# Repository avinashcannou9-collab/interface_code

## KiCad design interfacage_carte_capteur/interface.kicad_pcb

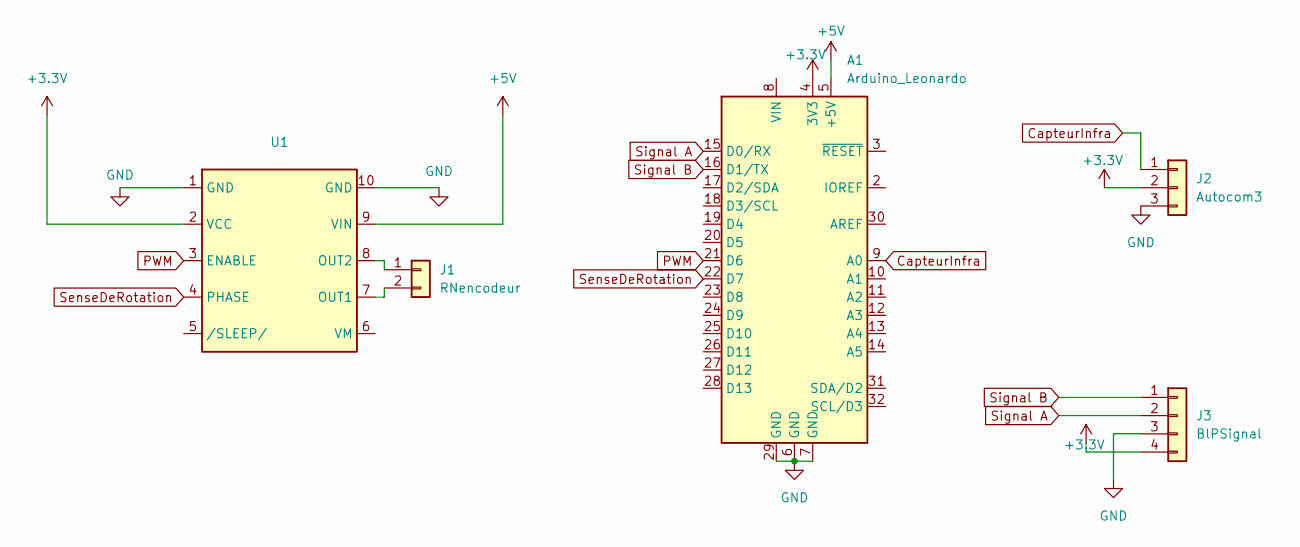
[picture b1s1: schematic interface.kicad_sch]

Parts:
A1: Arduino_Leonardo; Arduino_UNO_R3
J1: RNencodeur; Autocom2
J2: Autocom3
J3: BlPSignal; Autocom4
U1: DIP-10_W7.62mm_LongPads

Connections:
+3.3V: A1.4 (3V3), J2.2, J3.4, U1.2 (VCC)
+5V: A1.5 (+5V), U1.9 (VIN)
CapteurInfra: A1.9 (A0), J2.1
GND: A1.6 (GND), A1.7 (GND), A1.29 (GND), J2.3, J3.3, U1.1 (GND), U1.10 (GND)
unnamed: J1.1, U1.8 (OUT2)
unnamed: J1.2, U1.7 (OUT1)
PWM: A1.21 (D6), U1.3 (ENABLE)
SenseDeRotation: A1.22 (D7), U1.4 (PHASE)
Signal A: A1.15 (D0/RX), J3.2
Signal B: A1.16 (D1/TX), J3.1

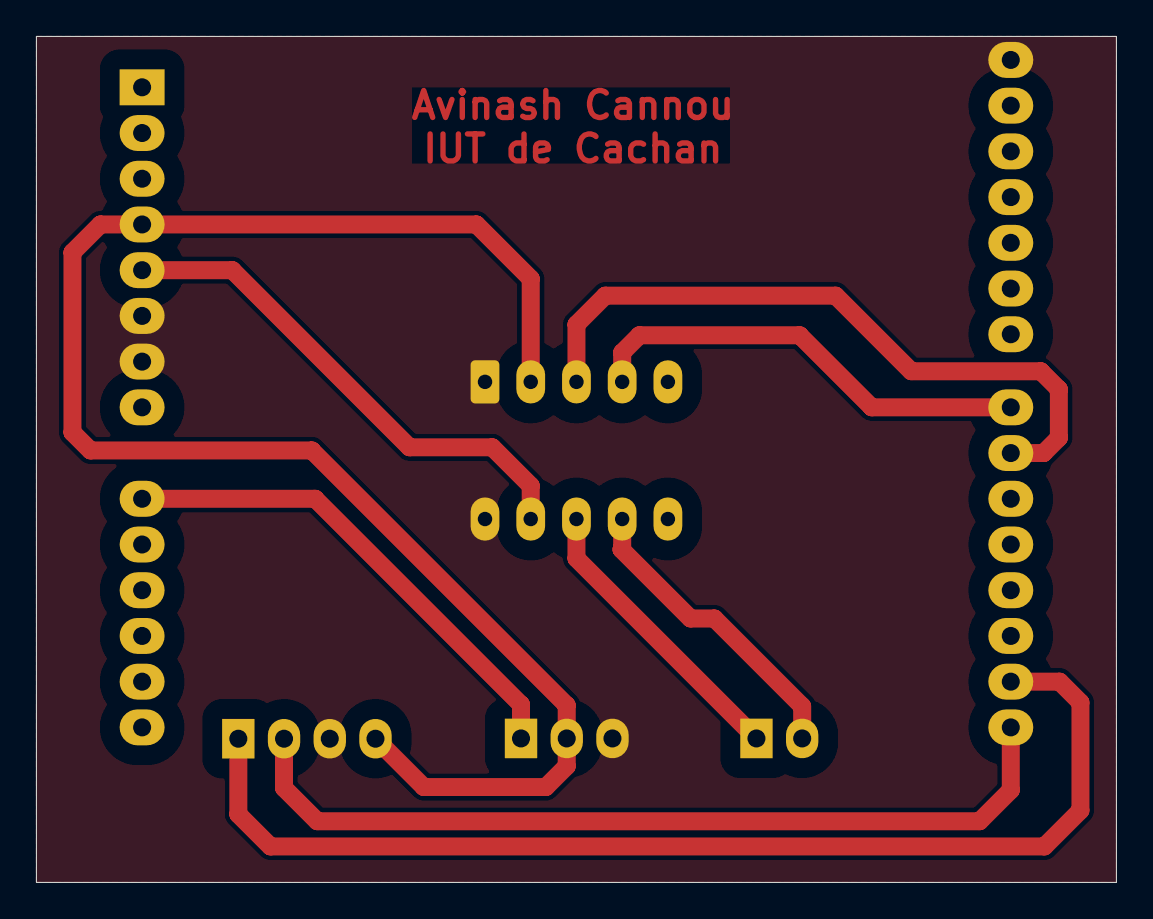
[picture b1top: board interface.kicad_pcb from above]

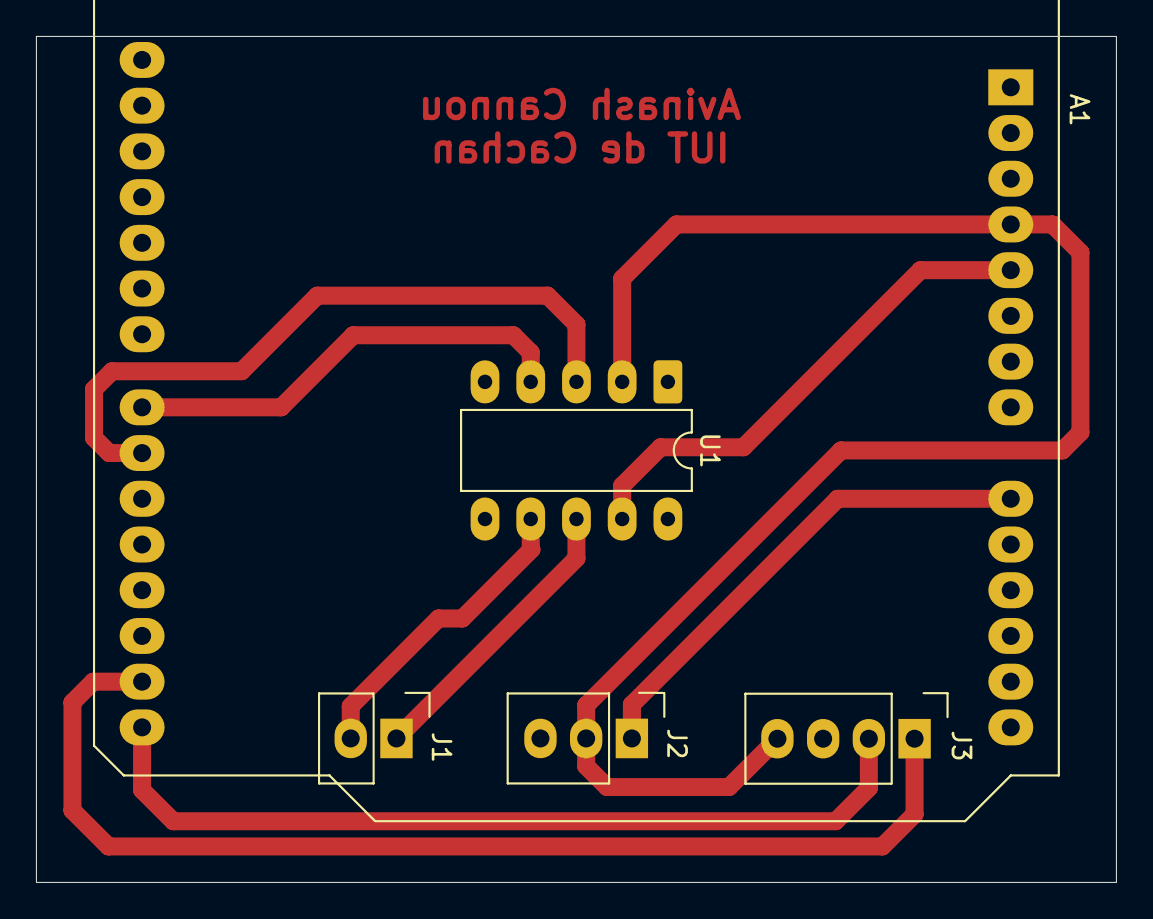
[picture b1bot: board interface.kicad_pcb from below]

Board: 2 copper layers, 60.0 x 47.0 mm, 5 parts (5 on the bottom side), 10 nets.

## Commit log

2026-06-04 2nd commit
2026-06-09 Test image de fond
2026-06-09 Hardware.h
2026-06-09 moteur fonctionne
2026-06-09 fin de scéance
2026-06-10 commite 3
2026-06-11 commite 4
2026-06-11 ca marche!!!!!
2026-06-11 jeu complet a améliorer
2026-06-15 jeu + seconde page chrono
2026-06-18 fin de projet
2026-06-23 Code + Kicad
